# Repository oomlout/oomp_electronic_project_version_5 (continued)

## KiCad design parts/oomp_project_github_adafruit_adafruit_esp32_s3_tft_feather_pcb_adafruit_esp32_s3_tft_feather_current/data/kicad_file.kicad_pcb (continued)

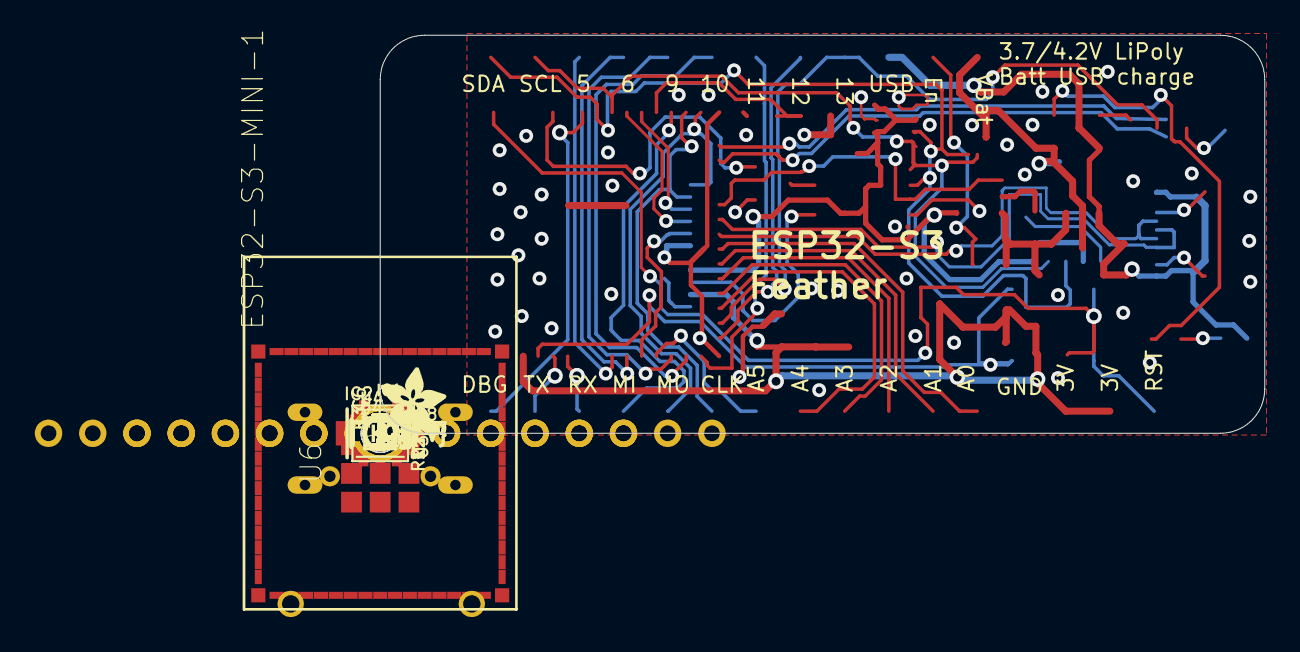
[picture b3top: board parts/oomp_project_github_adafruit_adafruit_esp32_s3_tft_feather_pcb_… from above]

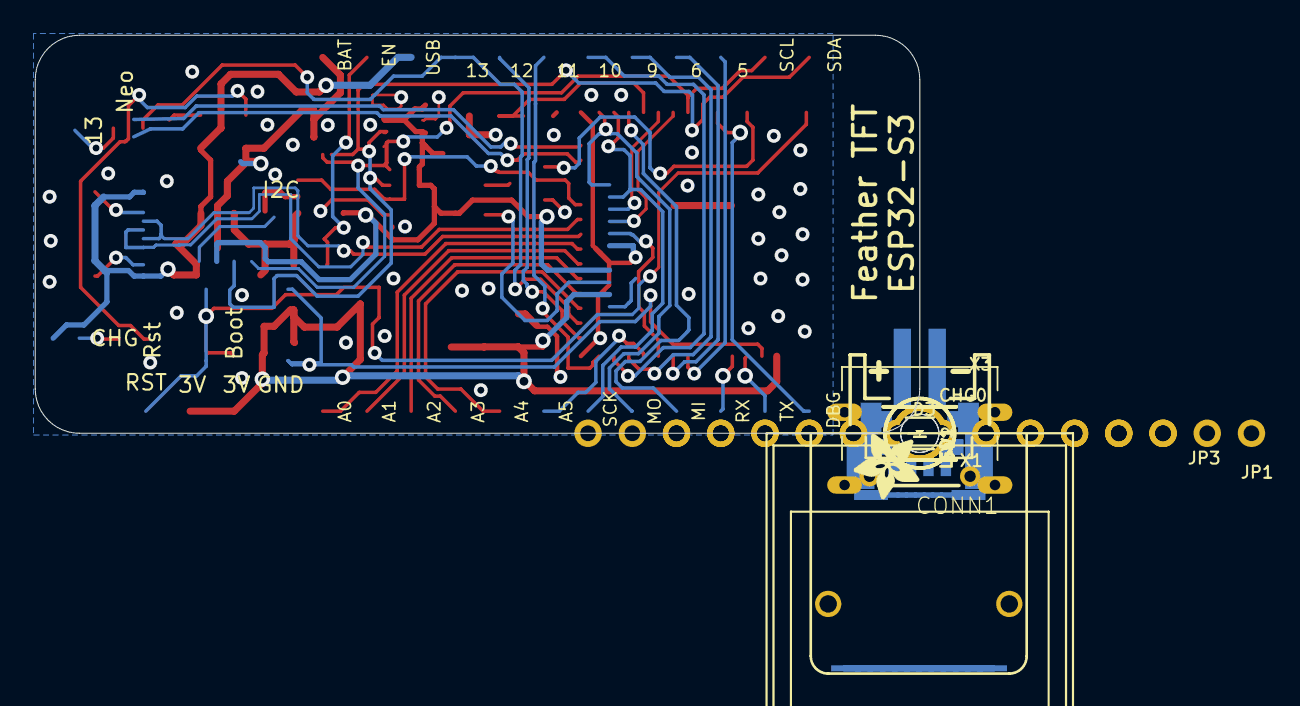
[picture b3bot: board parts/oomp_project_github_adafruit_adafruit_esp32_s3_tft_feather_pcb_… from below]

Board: 2 copper layers, 50.8 x 22.9 mm, 56 parts (16 on the bottom side), 48 nets.

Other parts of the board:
U$7: PCBFEAT-REV-040
U$9, U$54: ADAFRUIT_3.5MM
UNK_HOLE_0: dummyfp0
UNK_HOLE_1: dummyfp1

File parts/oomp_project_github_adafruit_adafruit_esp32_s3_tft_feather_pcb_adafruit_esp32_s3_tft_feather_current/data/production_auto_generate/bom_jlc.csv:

Comment,Designator,Footprint,LCSC Part #
,JP3,Adafruit ESP32-S3 TFT Feather-import-fps:1X12_ROUND_MIN,C7501588
,JP1,Adafruit ESP32-S3 TFT Feather-import-fps:1X16_ROUND_MIN,C7501270
,"U$9,U$54",Adafruit ESP32-S3 TFT Feather-import-fps:ADAFRUIT_3.5MM,
,U$7,Adafruit ESP32-S3 TFT Feather-import-fps:PCBFEAT-REV-040,
,TP1,Adafruit ESP32-S3 TFT Feather-import-fps:TESTPOINT_ROUND_1.5MM_NO,
100K,"R7,R12",Adafruit ESP32-S3 TFT Feather-import-fps:0603-NO,C25803
10K,R3,Adafruit ESP32-S3 TFT Feather-import-fps:RESPACK_4X0603,C98220
10uF,"C1,C2,C7,C9,C12",Adafruit ESP32-S3 TFT Feather-import-fps:0805-NO,
10µF,"C3,C6,C8",Adafruit ESP32-S3 TFT Feather-import-fps:0805-NO,
1Meg,R17,Adafruit ESP32-S3 TFT Feather-import-fps:0603-NO,C2907003
1uF,"C4,C5,C10,C11",Adafruit ESP32-S3 TFT Feather-import-fps:0603-NO,C5673
22,R11,Adafruit ESP32-S3 TFT Feather-import-fps:0603-NO,C23345
5.1K,"R1,R2,R4,R5,R8,R10",Adafruit ESP32-S3 TFT Feather-import-fps:0603-NO,C23186
AP2112-3.3,"U2,U5",Adafruit ESP32-S3 TFT Feather-import-fps:SOT23-5,
BME280,U4,Adafruit ESP32-S3 TFT Feather-import-fps:BME280,
BME680,IC2,Adafruit ESP32-S3 TFT Feather-import-fps:BME680,
BSS138,Q1,Adafruit ESP32-S3 TFT Feather-import-fps:SOT23-R,C52895
DISP_LCD_GENERIC_SPI_1.14IN_240X135_WRAPUNDER,DISP1,Adafruit ESP32-S3 TFT Feather-import-fps:TFT_1.14IN_240X135_WRAPUNDER,
DMG3415U,Q3,Adafruit ESP32-S3 TFT Feather-import-fps:SOT23-R,
ESP32-S3-MINI-1,U6,Adafruit ESP32-S3 TFT Feather-import-fps:QFN60_ESP32-S2-MINI-1_EXP,
FIDUCIAL_1MM,"U$34,U$35,U$55,U$56",Adafruit ESP32-S3 TFT Feather-import-fps:FIDUCIAL_1MM,
JSTPH,X1,Adafruit ESP32-S3 TFT Feather-import-fps:JSTPH2_BATT,
KMR2,"SW1,SW2",Adafruit ESP32-S3 TFT Feather-import-fps:BTN_KMR2_4.6X2.8,
LC709203F/MH,IC1,Adafruit ESP32-S3 TFT Feather-import-fps:WLCSP9,
MBR540,D4,Adafruit ESP32-S3 TFT Feather-import-fps:SOD-123,
MCP73831T-2ACI/OT,U3,Adafruit ESP32-S3 TFT Feather-import-fps:SOT23-5,
ORANGE,CHG0,Adafruit ESP32-S3 TFT Feather-import-fps:CHIPLED_0603_NOOUTLINE,
RED,D3,Adafruit ESP32-S3 TFT Feather-import-fps:CHIPLED_0603_NOOUTLINE,
STEMMA_I2C_QTRA,CONN1,Adafruit ESP32-S3 TFT Feather-import-fps:JST_SH4_RA,
USB C,X3,Adafruit ESP32-S3 TFT Feather-import-fps:USB_C_CUSB31-CFM2AX-01-X,
WS2812B_SK6805_1515,LED1,Adafruit ESP32-S3 TFT Feather-import-fps:SK6805_1515,

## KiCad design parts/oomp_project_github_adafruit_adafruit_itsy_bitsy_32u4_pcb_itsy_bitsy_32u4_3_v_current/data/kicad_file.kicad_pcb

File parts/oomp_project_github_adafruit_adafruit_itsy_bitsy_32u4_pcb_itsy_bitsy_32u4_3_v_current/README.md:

# Project adafruit/Adafruit-ItsyBitsy-32u4-PCB Itsy Bitsy 32u4 3 V current

[View the project on GitHub](https://github.com/adafruit/Adafruit-ItsyBitsy-32u4-PCB/blob/master/Itsy%20Bitsy%2032u4%203V.brd)

[Open the interactive board explorer (GitHub Pages)](https://oomlout.github.io/oomp_electronic_project_version_5/parts/oomp_project_github_adafruit_adafruit_itsy_bitsy_32u4_pcb_itsy_bitsy_32u4_3_v_current/board_explorer.html)

[Browse this project category](../../navigation/oomp/project/github/adafruit/adafruit_itsy_bitsy_32u4_pcb/itsy_bitsy_32u4_3_v/README.md)

Project adafruit/Adafruit-ItsyBitsy-32u4-PCB Itsy Bitsy 32u4 3 V current is a KiCad project containing 54 extracted component records. The catalogue matcher linked 13 physical placements to OOMP parts.

## Project snapshot

| Item | Count |
| --- | ---: |
| Components | 54 |
| PCB footprints | 26 |
| Mounting and locating holes | 2 |
| Matched OOMP mounting-hole items | 2 |
| Schematic symbols | 53 |
| Matched OOMP components | 13 |
| Unmatched physical components | 8 |
| Front-side placements | 21 |
| Back-side placements | 0 |
| Project version | `current` |
| Git ref | `master` |

## Board

[Original KiCad files](https://github.com/oomlout/oomp_electronic_project_version_5/tree/main/parts/oomp_project_github_adafruit_adafruit_itsy_bitsy_32u4_pcb_itsy_bitsy_32u4_3_v_current/data/original) · [OOMP KiCad design and local libraries](https://github.com/oomlout/oomp_electronic_project_version_5/tree/main/parts/oomp_project_github_adafruit_adafruit_itsy_bitsy_32u4_pcb_itsy_bitsy_32u4_3_v_current/data/oomp_design) · [Conversion / skipped-item report](https://github.com/oomlout/oomp_electronic_project_version_5/blob/main/parts/oomp_project_github_adafruit_adafruit_itsy_bitsy_32u4_pcb_itsy_bitsy_32u4_3_v_current/data/oomp_design/conversion_report.yaml)

The OOMP design is a separate copy. Only symbols and footprints verified against unchanged installed KiCad masters are replaced; custom and modified items are retained.

- Approximate size: **35.56 mm × 17.78 mm**
- Outline source: `KiCad Edge.Cuts`
- Placement drawing: [view `board.svg`](https://github.com/oomlout/oomp_electronic_project_version_5/blob/main/parts/oomp_project_github_adafruit_adafruit_itsy_bitsy_32u4_pcb_itsy_bitsy_32u4_3_v_current/data/generated_data/src/board.svg)
- PNG placement drawing: [view `board.png`](https://github.com/oomlout/oomp_electronic_project_version_5/blob/main/parts/oomp_project_github_adafruit_adafruit_itsy_bitsy_32u4_pcb_itsy_bitsy_32u4_3_v_current/data/generated_data/src/board.png)
- 300-pixel placement preview: [view `board_300.png`](https://github.com/oomlout/oomp_electronic_project_version_5/blob/main/parts/oomp_project_github_adafruit_adafruit_itsy_bitsy_32u4_pcb_itsy_bitsy_32u4_3_v_current/data/generated_data/src/board_300.png)
- Placement drawing with pin names: [view `board_pins.svg`](https://github.com/oomlout/oomp_electronic_project_version_5/blob/main/parts/oomp_project_github_adafruit_adafruit_itsy_bitsy_32u4_pcb_itsy_bitsy_32u4_3_v_current/data/generated_data/src/board_pins.svg)
- PNG drawing with pin names: [view `board_pins.png`](https://github.com/oomlout/oomp_electronic_project_version_5/blob/main/parts/oomp_project_github_adafruit_adafruit_itsy_bitsy_32u4_pcb_itsy_bitsy_32u4_3_v_current/data/generated_data/src/board_pins.png)
- 300-pixel pin preview: [view `board_pins_300.png`](https://github.com/oomlout/oomp_electronic_project_version_5/blob/main/parts/oomp_project_github_adafruit_adafruit_itsy_bitsy_32u4_pcb_itsy_bitsy_32u4_3_v_current/data/generated_data/src/board_pins_300.png)
- Bottom placement drawing: [view `board_bottom.svg`](https://github.com/oomlout/oomp_electronic_project_version_5/blob/main/parts/oomp_project_github_adafruit_adafruit_itsy_bitsy_32u4_pcb_itsy_bitsy_32u4_3_v_current/data/generated_data/src/board_bottom.svg)
- Bottom PNG placement drawing: [view `board_bottom.png`](https://github.com/oomlout/oomp_electronic_project_version_5/blob/main/parts/oomp_project_github_adafruit_adafruit_itsy_bitsy_32u4_pcb_itsy_bitsy_32u4_3_v_current/data/generated_data/src/board_bottom.png)
- 300-pixel bottom preview: [view `board_bottom_300.png`](https://github.com/oomlout/oomp_electronic_project_version_5/blob/main/parts/oomp_project_github_adafruit_adafruit_itsy_bitsy_32u4_pcb_itsy_bitsy_32u4_3_v_current/data/generated_data/src/board_bottom_300.png)
- Bottom placement drawing with pin names: [view `board_pins_bottom.svg`](https://github.com/oomlout/oomp_electronic_project_version_5/blob/main/parts/oomp_project_github_adafruit_adafruit_itsy_bitsy_32u4_pcb_itsy_bitsy_32u4_3_v_current/data/generated_data/src/board_pins_bottom.svg)
- Bottom PNG drawing with pin names: [view `board_pins_bottom.png`](https://github.com/oomlout/oomp_electronic_project_version_5/blob/main/parts/oomp_project_github_adafruit_adafruit_itsy_bitsy_32u4_pcb_itsy_bitsy_32u4_3_v_current/data/generated_data/src/board_pins_bottom.png)
- 300-pixel bottom pin preview: [view `board_pins_bottom_300.png`](https://github.com/oomlout/oomp_electronic_project_version_5/blob/main/parts/oomp_project_github_adafruit_adafruit_itsy_bitsy_32u4_pcb_itsy_bitsy_32u4_3_v_current/data/generated_data/src/board_pins_bottom_300.png)
- Mechanical drawing: [view `board_mechanical.svg`](https://github.com/oomlout/oomp_electronic_project_version_5/blob/main/parts/oomp_project_github_adafruit_adafruit_itsy_bitsy_32u4_pcb_itsy_bitsy_32u4_3_v_current/data/generated_data/src/board_mechanical.svg)
- Mechanical PNG: [view `board_mechanical.png`](https://github.com/oomlout/oomp_electronic_project_version_5/blob/main/parts/oomp_project_github_adafruit_adafruit_itsy_bitsy_32u4_pcb_itsy_bitsy_32u4_3_v_current/data/generated_data/src/board_mechanical.png)
- 300-pixel mechanical preview: [view `board_mechanical_300.png`](https://github.com/oomlout/oomp_electronic_project_version_5/blob/main/parts/oomp_project_github_adafruit_adafruit_itsy_bitsy_32u4_pcb_itsy_bitsy_32u4_3_v_current/data/generated_data/src/board_mechanical_300.png)
- Open the board explorer on GitHub Pages: [explore this board](https://oomlout.github.io/oomp_electronic_project_version_5/parts/oomp_project_github_adafruit_adafruit_itsy_bitsy_32u4_pcb_itsy_bitsy_32u4_3_v_current/board_explorer.html)
- InteractiveHtmlBom generation is configured; install KiCad or set `KICAD_PYTHON` to its bundled Python to build `data/interactivehtmlbom/ibom.html`.

## Board with pins

## Bottom board with pins

The bottom view is mirrored horizontally so it is shown as viewed from beneath the assembled board.

## Mechanical layer

The table uses a board-relative origin at the minimum X/Y point of `Edge.Cuts`. This point is shown as **0,0** in the mechanical drawing; X increases right and Y increases down. Original KiCad coordinates are retained alongside it.

### Diameter 0.7 mm holes

| OOMP reference | Source | Name | Classification | Role | Board X (mm) | Board Y (mm) | OOMP part |
| --- | --- | --- | --- | --- | ---: | ---: | --- |
| `MH1` | `X3` | Mounting Hole 0.7 mm Round Unplated | `mechanical / mounting_hole / 0_7_mm / round / unplated` | locating | 4.445 | 6.940 | [`mechanical_mounting_hole_0_7_mm_round_unplated`](https://github.com/oomlout/oomp_electronic_version_5/tree/main/parts/mechanical_mounting_hole_0_7_mm_round_unplated) |
| `MH2` | `X3` | Mounting Hole 0.7 mm Round Unplated | `mechanical / mounting_hole / 0_7_mm / round / unplated` | locating | 4.445 | 10.840 | [`mechanical_mounting_hole_0_7_mm_round_unplated`](https://github.com/oomlout/oomp_electronic_version_5/tree/main/parts/mechanical_mounting_hole_0_7_mm_round_unplated) |

## Bill of materials

| References | Quantity | Description | Value | Footprint | OOMP part |
| --- | ---: | --- | --- | --- | --- |
| C6, C8 | 2 | Capacitor 10 uF 0805 | 10µF | `Itsy Bitsy 32u4 3V-import-fps:0805-NO` | [`electronic_capacitor_0805_10_micro_farad`](https://github.com/oomlout/oomp_electronic_version_5/tree/main/parts/electronic_capacitor_0805_10_micro_farad) |
| C7, C14 | 2 | Capacitor 1 uF 0603 | 1uF | `Itsy Bitsy 32u4 3V-import-fps:0603-NO` | [`electronic_capacitor_0603_1_micro_farad`](https://github.com/oomlout/oomp_electronic_version_5/tree/main/parts/electronic_capacitor_0603_1_micro_farad) |
| C9 | 1 | Capacitor 10 uF 0805 | 10uF | `Itsy Bitsy 32u4 3V-import-fps:0805-NO` | [`electronic_capacitor_0805_10_micro_farad`](https://github.com/oomlout/oomp_electronic_version_5/tree/main/parts/electronic_capacitor_0805_10_micro_farad) |
| D1, D4 | 2 | MBR120 | MBR120 | `Itsy Bitsy 32u4 3V-import-fps:SOD-123` | unmatched |
| IC1 | 1 | ATMEGA32U4-MU | ATMEGA32U4-MU | `Itsy Bitsy 32u4 3V-import-fps:TQFN44_7MM` | unmatched |
| IC2 | 1 | 74HCT1G125DBV | 74HCT1G125DBV | `Itsy Bitsy 32u4 3V-import-fps:SOT23-5` | unmatched |
| JP1 | 1 | Connector Header PH2.54-1X5P-H25 |  | `Itsy Bitsy 32u4 3V-import-fps:1X05_ROUND` | [`electronic_connector_header_2_54_mm_pitch_through_hole_5_pin`](https://github.com/oomlout/oomp_electronic_version_5/tree/main/parts/electronic_connector_header_2_54_mm_pitch_through_hole_5_pin) |
| JP2, JP4 | 2 | Connector Header KH-2.54PH180-1X14P-L11.5 |  | `Itsy Bitsy 32u4 3V-import-fps:1X14_ROUND70` | [`electronic_connector_header_2_54_mm_pitch_through_hole_14_pin`](https://github.com/oomlout/oomp_electronic_version_5/tree/main/parts/electronic_connector_header_2_54_mm_pitch_through_hole_14_pin) |
| L0 | 1 | LED Red 0805 | RED | `Itsy Bitsy 32u4 3V-import-fps:CHIPLED_0805_NOOUTLINE` | [`electronic_led_0805_red`](https://github.com/oomlout/oomp_electronic_version_5/tree/main/parts/electronic_led_0805_red) |
| R4, R5 | 2 | Resistor 22 Ohm 0603 | 22 | `Itsy Bitsy 32u4 3V-import-fps:0603-NO` | [`electronic_resistor_0603_22_ohm`](https://github.com/oomlout/oomp_electronic_version_5/tree/main/parts/electronic_resistor_0603_22_ohm) |
| R7 | 1 | Resistor 2200 Ohm 0603 | 2.2K | `Itsy Bitsy 32u4 3V-import-fps:0603-NO` | [`electronic_resistor_0603_2200_ohm`](https://github.com/oomlout/oomp_electronic_version_5/tree/main/parts/electronic_resistor_0603_2200_ohm) |
| R9 | 1 | Resistor 100000 Ohm 0603 | 100k | `Itsy Bitsy 32u4 3V-import-fps:0603-NO` | [`electronic_resistor_0603_100000_ohm`](https://github.com/oomlout/oomp_electronic_version_5/tree/main/parts/electronic_resistor_0603_100000_ohm) |
| SW1 | 1 | SPST_TACT-KMR2 | SPST_TACT-KMR2 | `Itsy Bitsy 32u4 3V-import-fps:KMR2` | unmatched |
| U2 | 1 | AP2112K | AP2112K | `Itsy Bitsy 32u4 3V-import-fps:SOT23-5` | unmatched |
| X3 | 1 | microUSB | microUSB | `Itsy Bitsy 32u4 3V-import-fps:4UCONN_20329_V2` | unmatched |
| Y1 | 1 | 8MHz | 8MHz | `Itsy Bitsy 32u4 3V-import-fps:RESONATOR-SMD` | unmatched |

## Main nets

| Net | Pads | Components |
| --- | ---: | --- |
| `GND` | 27 | C6, C7, C8, C9, C14, IC1, IC2, JP1, JP2, JP4, L0, SW1, U2, X3, Y1 |
| `+3V3` | 11 | C7, C8, C9, IC1, JP4, U2 |
| `VMAX` | 7 | C6, D1, D4, IC2, JP4, R9, U2 |
| `RST` | 4 | IC1, JP4, SW1 |
| `VBUS` | 4 | D1, IC1, JP2, X3 |
| `AREF` | 3 | C14, IC1, JP4 |
| `D13` | 3 | IC1, JP2, R7 |
| `EN` | 3 | JP1, R9, U2 |
| `A0` | 2 | IC1, JP4 |
| `A1` | 2 | IC1, JP4 |
| `A2` | 2 | IC1, JP4 |
| `A3` | 2 | IC1, JP4 |
| `A4` | 2 | IC1, JP4 |
| `A5` | 2 | IC1, JP4 |
| `D+` | 2 | IC1, R5 |
| `D-` | 2 | IC1, R4 |
| `D0` | 2 | IC1, JP2 |
| `D1` | 2 | IC1, JP2 |
| `D10` | 2 | IC1, JP2 |
| `D11` | 2 | IC1, JP2 |

## Design notes

- The extracted board outline is approximately 35.56 mm by 17.78 mm.
- Placement data contains 21 front-side and 0 back-side components.

## Review notes

- 8 physical component records are not yet matched to an OOMP part.

- Part identities needing a manufacturer/LCSC decision: [`lcsc_review.yaml`](https://github.com/oomlout/oomp_electronic_project_version_5/blob/main/parts/oomp_project_github_adafruit_adafruit_itsy_bitsy_32u4_pcb_itsy_bitsy_32u4_3_v_current/data/generated_data/lcsc_review.yaml)
- Browser-only research and datasheet queue: [`browser_research_queue.md`](https://github.com/oomlout/oomp_electronic_project_version_5/blob/main/parts/oomp_project_github_adafruit_adafruit_itsy_bitsy_32u4_pcb_itsy_bitsy_32u4_3_v_current/data/generated_data/browser_research_queue.md)

## Generated source bundle

- Project image assets: [`data/generated_data/src`](https://github.com/oomlout/oomp_electronic_project_version_5/tree/main/parts/oomp_project_github_adafruit_adafruit_itsy_bitsy_32u4_pcb_itsy_bitsy_32u4_3_v_current/data/generated_data/src)
- Copied component source manifest: `data/project_source/manifest.yaml` (generated locally and ignored by Git)
- Matched OOMP source parts copied: 8

## Source files

- Schematic: `data/kicad_file.kicad_sch`
- PCB: `data/kicad_file.kicad_pcb`

---

Generated deterministically by `kicad_agents.project_summary_agent`; no LLM-authored content is used.

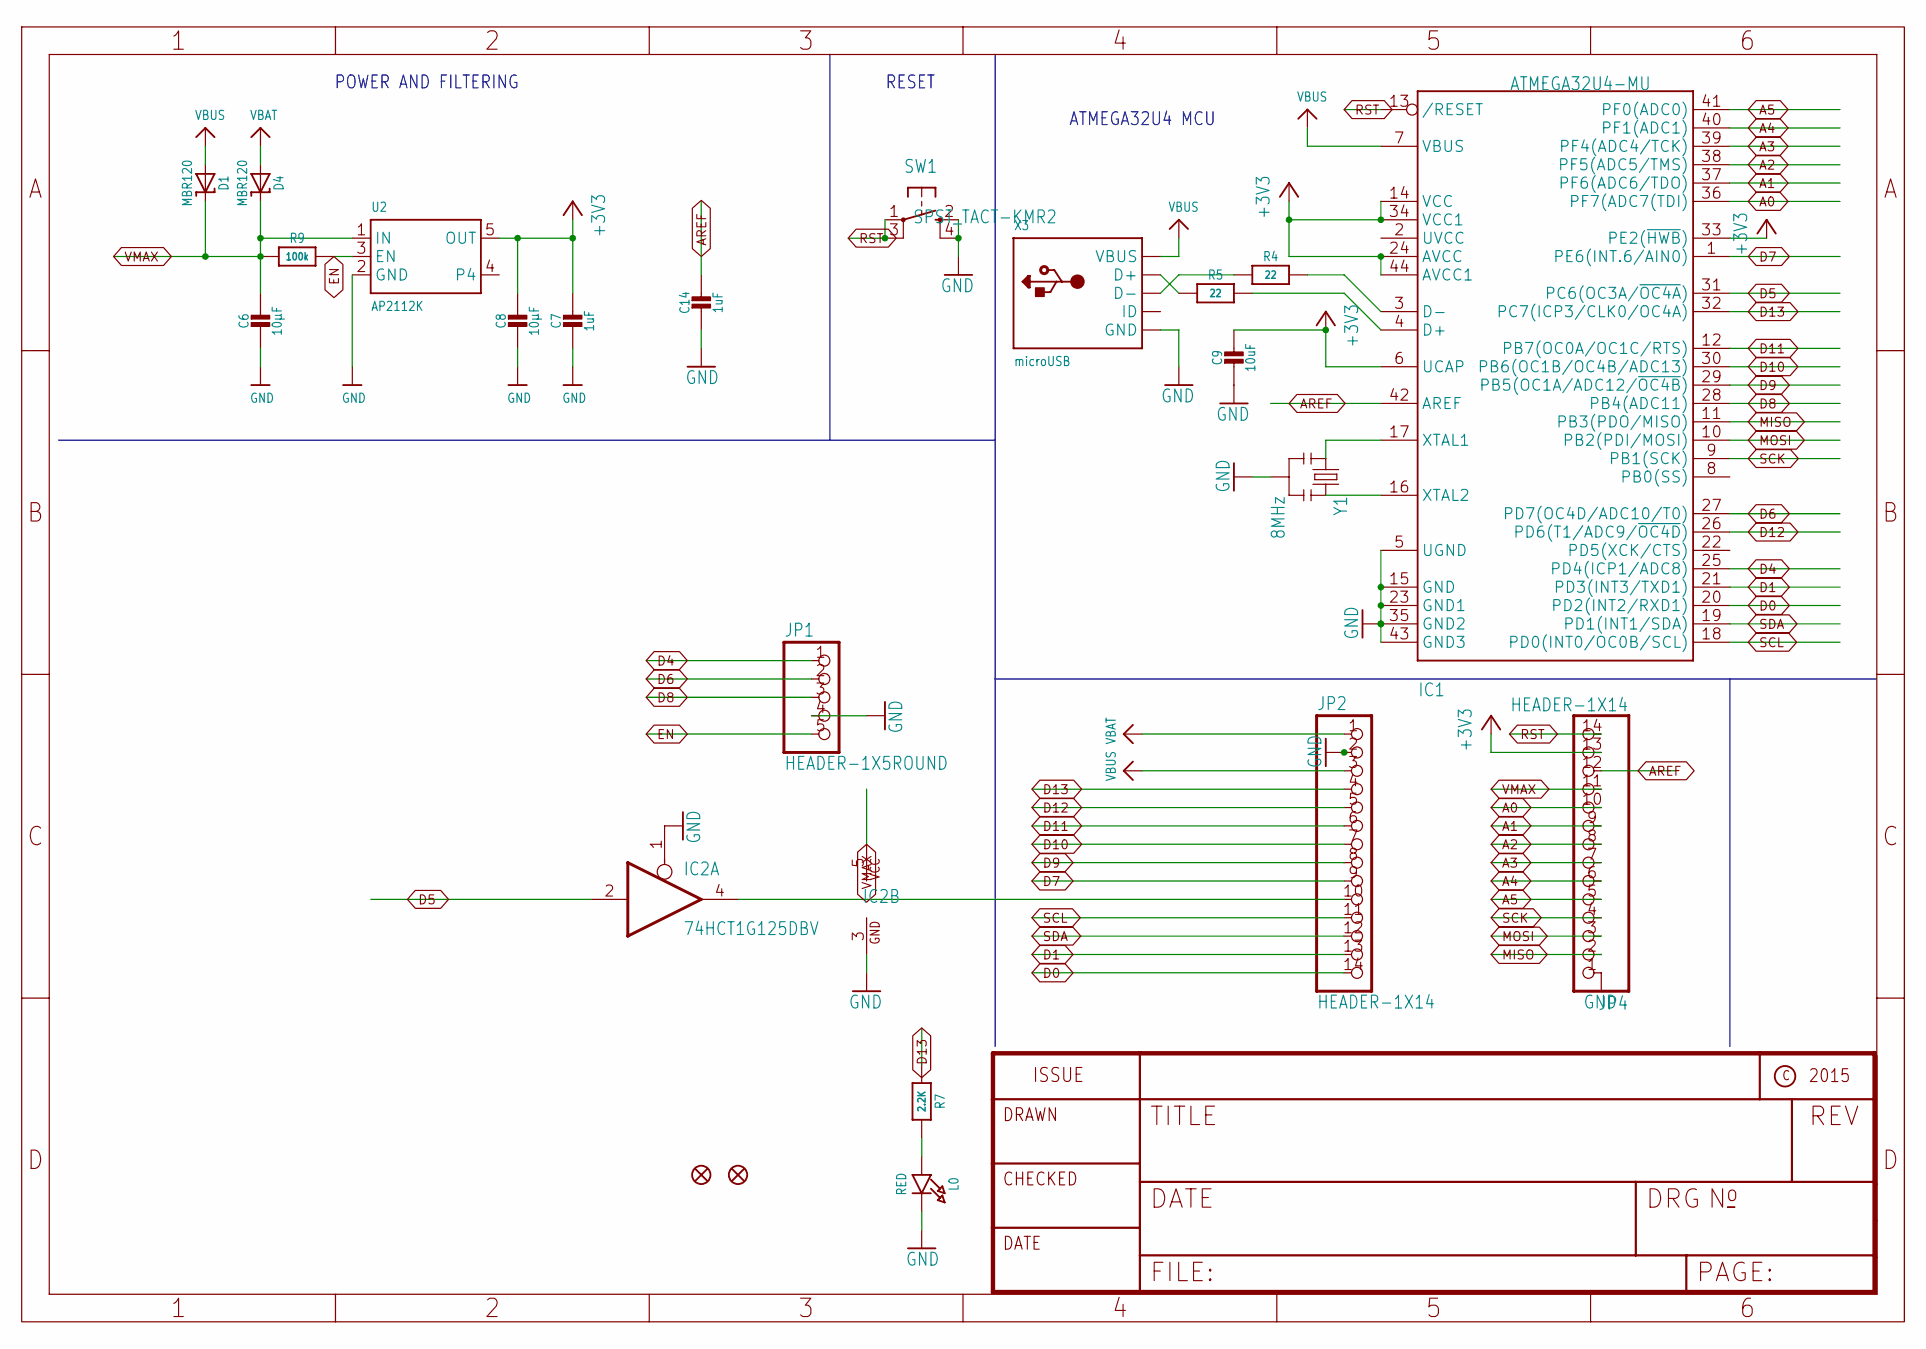
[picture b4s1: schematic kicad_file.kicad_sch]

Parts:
C6, C8: 10µF; 0805-NO
C7, C14: 1uF; 0603-NO
C9: 10uF; 0805-NO
D1, D4: MBR120; SOD-123
IC1: ATMEGA32U4-MU; TQFN44_7MM
IC2: 74HCT1G125DBV; SOT23-5
JP1: HEADER-1X5ROUND; 1X05_ROUND
JP2, JP4: HEADER-1X14; 1X14_ROUND70
L0: RED; CHIPLED_0805_NOOUTLINE
R4, R5: 22; 0603-NO
R7: 2.2K; 0603-NO
R9: 100k; 0603-NO
SW1: SPST_TACT-KMR2; KMR2
U2: AP2112K; SOT23-5
U$34, U$35: FIDUCIAL""; FIDUCIAL_1MM
X3: microUSB; 4UCONN_20329_V2
Y1: 8MHz; RESONATOR-SMD

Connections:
+3V3: C7.1, C8.1, C9.1, IC1.6 (UCAP), IC1.14 (VCC), IC1.24 (AVCC), IC1.33 (PE2(~HWB)), IC1.34 (VCC1), IC1.44 (AVCC1), JP4.13, U2.5 (OUT)
A0: IC1.36 (PF7(ADC7(TDI)), JP4.10
A1: IC1.37 (PF6(ADC6/TDO)), JP4.9
A2: IC1.38 (PF5(ADC5/TMS)), JP4.8
A3: IC1.39 (PF4(ADC4/TCK)), JP4.7
A4: IC1.40 (PF1(ADC1)), JP4.6
A5: IC1.41 (PF0(ADC0)), JP4.5
AREF: C14.1, IC1.42 (AREF), JP4.12
D0: IC1.20 (PD2(INT2/RXD1)), JP2.14
D1: IC1.21 (PD3(INT3/TXD1)), JP2.13
D4: IC1.25 (PD4(ICP1/ADC8)), JP1.1
D5: IC1.31 (PC6(OC3A/~OC4A)), IC2.2 (I)
D5_OUT: IC2.4 (O), JP2.10
D6: IC1.27 (PD7(OC4D/ADC10/T0)), JP1.2
D7: IC1.1 (PE6(INT.6/AIN0)), JP2.9
D8: IC1.28 (PB4(ADC11)), JP1.3
D9: IC1.29 (PB5(OC1A/ADC12/~OC4B)), JP2.8
D10: IC1.30 (PB6(OC1B/OC4B/ADC13)), JP2.7
D11: IC1.12 (PB7(OC0A/OC1C/RTS)), JP2.6
D12: IC1.26 (PD6(T1/ADC9/~OC4D)), JP2.5
D13: IC1.32 (PC7(ICP3/CLK0/OC4A)), JP2.4, R7.1
D+: IC1.4 (D+), R5.2
D-: IC1.3 (D-), R4.2
EN: JP1.5, R9.2, U2.3 (EN)
GND: C6.2, C7.2, C8.2, C9.2, C14.2, IC1.5 (UGND), IC1.15 (GND), IC1.23 (GND1), IC1.35 (GND2), IC1.43 (GND3), IC2.1 (OE), IC2.3 (GND), JP1.4, JP2.2, JP4.1, L0.C, SW1.2 (S), SW1.4 (S1), U2.2 (GND), X3.BASE@1 (GND), X3.BASE@2 (GND), X3.GND, X3.SPRT@1 (GND), X3.SPRT@2 (GND), X3.SPRT@3 (GND), X3.SPRT@4 (GND), Y1.2
MISO: IC1.11 (PB3(PDO/MISO)), JP4.2
MOSI: IC1.10 (PB2(PDI/MOSI)), JP4.3
unnamed: L0.A, R7.2
unnamed: IC1.16 (XTAL2), Y1.3
unnamed: IC1.17 (XTAL1), Y1.1
unnamed: R5.1, X3.D+
unnamed: R4.1, X3.D-
RST: IC1.13 (/RESET), JP4.14, SW1.1, SW1.3 (P1)
SCK: IC1.9 (PB1(SCK)), JP4.4
SCL: IC1.18 (PD0(INT0/OC0B/SCL)), JP2.11
SDA: IC1.19 (PD1(INT1/SDA)), JP2.12
VBAT: D4.A, JP2.1
VBUS: D1.A, IC1.7 (VBUS), JP2.3, X3.VBUS
VMAX: C6.1, D1.C, D4.C, IC2.5 (VCC), JP4.11, R9.1, U2.1 (IN)

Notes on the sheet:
POWER AND FILTERING
RESET
ATMEGA32U4 MCU

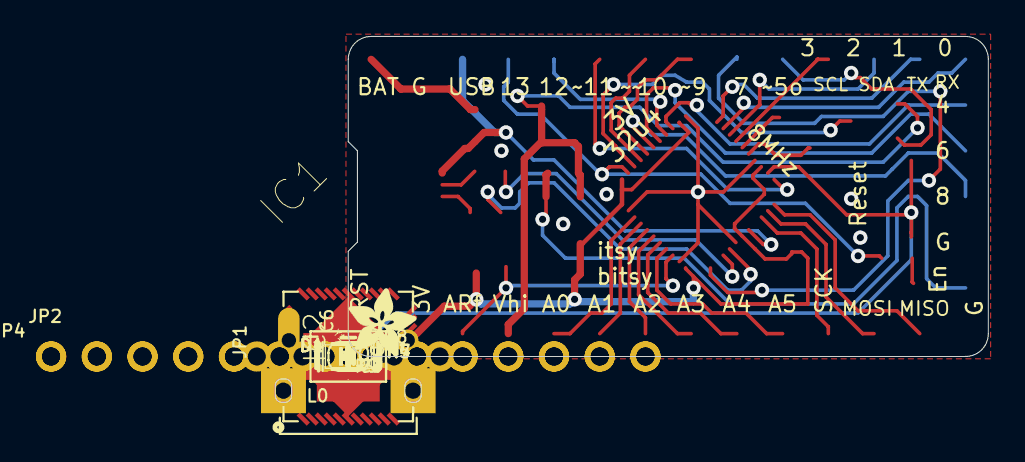
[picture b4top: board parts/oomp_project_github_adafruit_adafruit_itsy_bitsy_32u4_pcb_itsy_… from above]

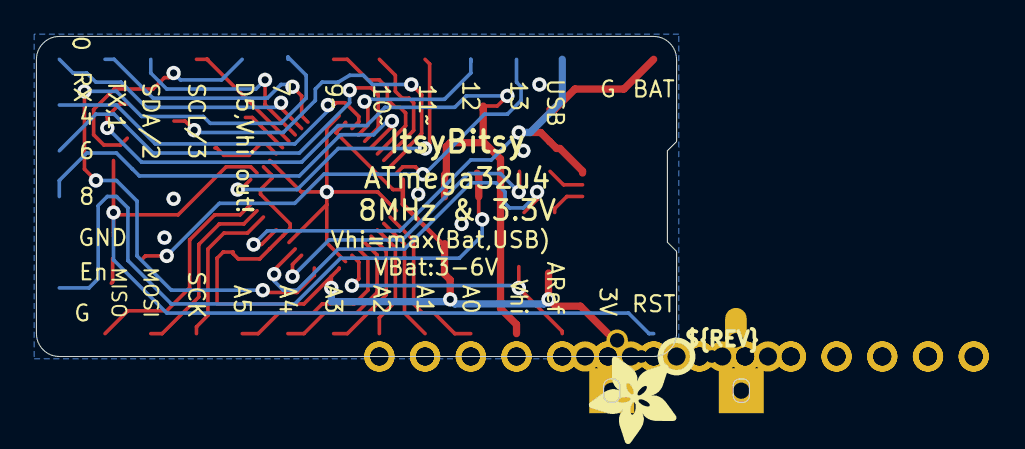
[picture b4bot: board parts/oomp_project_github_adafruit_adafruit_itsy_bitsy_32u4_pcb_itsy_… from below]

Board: 2 copper layers, 35.6 x 17.8 mm, 26 parts (2 on the bottom side), 39 nets.

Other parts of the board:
U$2: PCBFEAT-REV-040
U$4: ADAFRUIT_5MM
U$7: ADAFRUIT_3.5MM

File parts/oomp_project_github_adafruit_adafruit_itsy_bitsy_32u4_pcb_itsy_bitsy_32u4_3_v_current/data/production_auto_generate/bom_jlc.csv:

Comment,Designator,Footprint,LCSC Part #
,JP1,Itsy Bitsy 32u4 3V-import-fps:1X05_ROUND,C42431835
,"JP2,JP4",Itsy Bitsy 32u4 3V-import-fps:1X14_ROUND70,C2905490
,U$7,Itsy Bitsy 32u4 3V-import-fps:ADAFRUIT_3.5MM,
,U$4,Itsy Bitsy 32u4 3V-import-fps:ADAFRUIT_5MM,
,U$2,Itsy Bitsy 32u4 3V-import-fps:PCBFEAT-REV-040,
100k,R9,Itsy Bitsy 32u4 3V-import-fps:0603-NO,C25803
10uF,C9,Itsy Bitsy 32u4 3V-import-fps:0805-NO,
10µF,"C6,C8",Itsy Bitsy 32u4 3V-import-fps:0805-NO,
1uF,"C7,C14",Itsy Bitsy 32u4 3V-import-fps:0603-NO,C5673
2.2K,R7,Itsy Bitsy 32u4 3V-import-fps:0603-NO,C4190
22,"R4,R5",Itsy Bitsy 32u4 3V-import-fps:0603-NO,C23345
74HCT1G125DBV,IC2,Itsy Bitsy 32u4 3V-import-fps:SOT23-5,
8MHz,Y1,Itsy Bitsy 32u4 3V-import-fps:RESONATOR-SMD,
AP2112K,U2,Itsy Bitsy 32u4 3V-import-fps:SOT23-5,
ATMEGA32U4-MU,IC1,Itsy Bitsy 32u4 3V-import-fps:TQFN44_7MM,
"FIDUCIAL""""","U$34,U$35",Itsy Bitsy 32u4 3V-import-fps:FIDUCIAL_1MM,
MBR120,"D1,D4",Itsy Bitsy 32u4 3V-import-fps:SOD-123,
microUSB,X3,Itsy Bitsy 32u4 3V-import-fps:4UCONN_20329_V2,
RED,L0,Itsy Bitsy 32u4 3V-import-fps:CHIPLED_0805_NOOUTLINE,
SPST_TACT-KMR2,SW1,Itsy Bitsy 32u4 3V-import-fps:KMR2,

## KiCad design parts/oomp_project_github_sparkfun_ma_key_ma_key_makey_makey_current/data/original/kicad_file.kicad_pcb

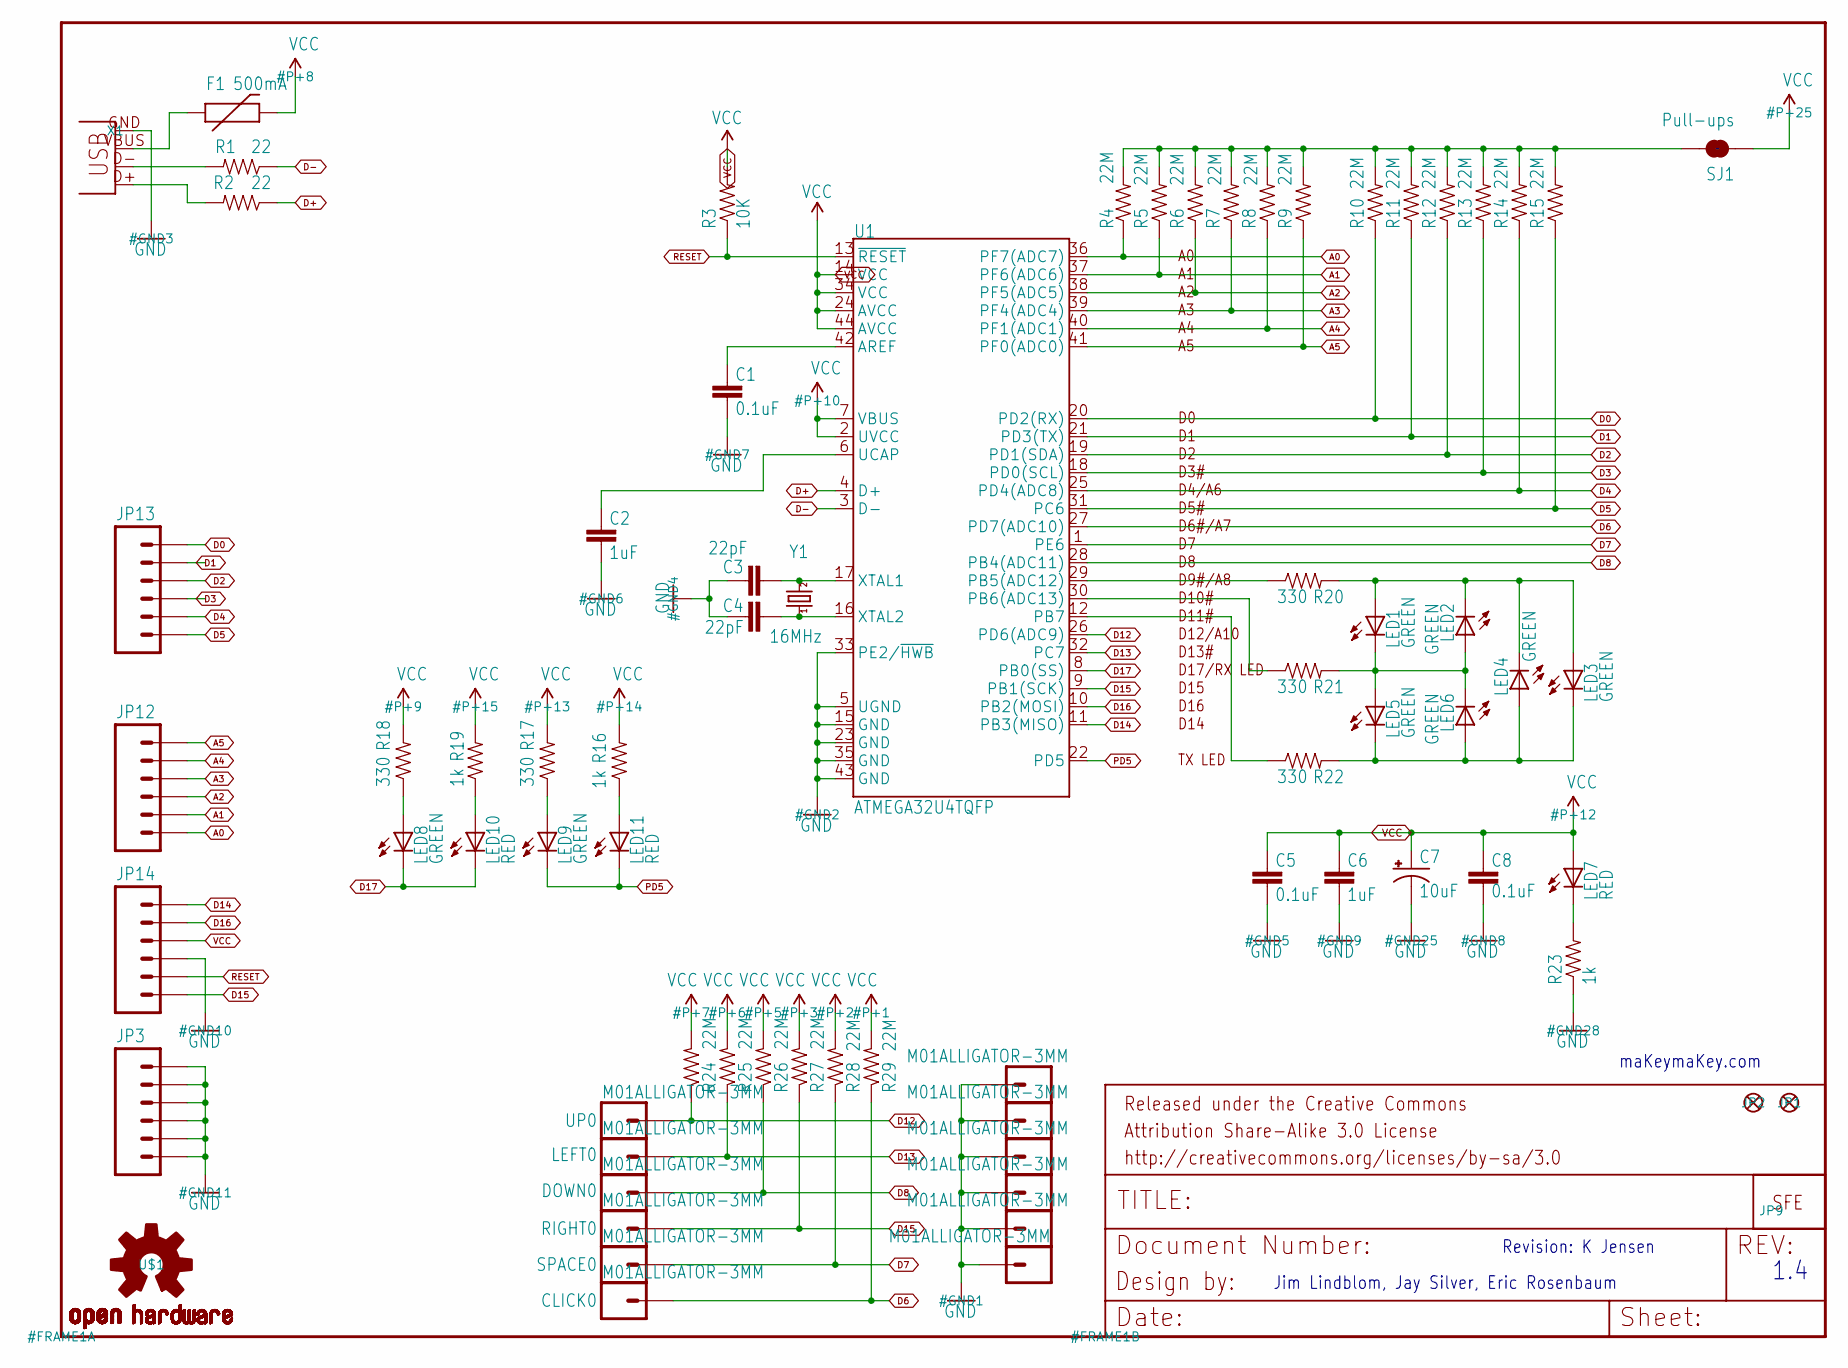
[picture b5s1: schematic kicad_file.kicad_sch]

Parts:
C1, C5, C8: 0.1uF; 0603-CAP
C2, C6: 1uF; 0603-CAP
C3, C4: 22pF; 0603-CAP
C7: 10uF; EIA3216
CLICK0: M01ALLIGATOR-3MM; 1X01_ALLIGATOR_3MM
DOWN0: M01ALLIGATOR-3MM; 1X01_ALLIGATOR_3MM
F1: 500mA; PTC-1206-WIDE
JP1, JP2: FIDUCIALUFIDUCIAL; MICRO-FIDUCIAL
JP3, JP12, JP13, JP14: M06SMD-STRAIGHT-COMBO; 1X06_SMD_STRAIGHT_COMBO
JP5, JP6, JP7, JP8, JP10, JP11: M01ALLIGATOR-3MM; 1X01_ALLIGATOR_3MM
JP9: LOGO-SFENEW; SFE-NEW-WEBLOGO
LED1, LED2, LED3, LED4, LED5, LED6: GREEN; LED-1206-BOTTOM
LED7, LED10, LED11: RED; LED-0603
LED8, LED9: GREEN; LED-0603
LEFT0: M01ALLIGATOR-3MM; 1X01_ALLIGATOR_3MM
R1, R2: 22; 0603-RES
R3: 10K; 0603-RES
R4, R5, R6, R7, R8, R9, R10, R11, R12, R13, R14, R15, R24, R25, R26, R27, R28, R29: 22M; 0603-RES
R16, R19, R23: 1k; 0603-RES
R17, R18, R20, R21, R22: 330; 0603-RES
RIGHT0: M01ALLIGATOR-3MM; 1X01_ALLIGATOR_3MM
SJ1: Pull-ups; SJ_2S-TRACE
SPACE0: M01ALLIGATOR-3MM; 1X01_ALLIGATOR_3MM
U1: ATMEGA32U4TQFP; TQFP44
U$1: OSHW-LOGOM; OSHW-LOGO-M
UP0: M01ALLIGATOR-3MM; 1X01_ALLIGATOR_3MM
X1: USBSMD; USB-MINIB
Y1: 16MHz; CRYSTAL-SMD-5X3

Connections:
A0: JP12.1, JP12.1-2 (1), R4.1, U1.36 (PF7(ADC7))
A1: JP12.2, JP12.2-2 (2), R5.1, U1.37 (PF6(ADC6))
A2: JP12.3, JP12.3-2 (3), R6.1, U1.38 (PF5(ADC5))
A3: JP12.4, JP12.4-2 (4), R7.1, U1.39 (PF4(ADC4))
A4: JP12.5, JP12.5-2 (5), R8.1, U1.40 (PF1(ADC1))
A5: JP12.6, JP12.6-2 (6), R9.1, U1.41 (PF0(ADC0))
AREF: C1.2, U1.42 (AREF)
D0: JP13.6, JP13.6-2 (6), R10.1, U1.20 (PD2(RX))
D1: JP13.5, JP13.5-2 (5), R11.1, U1.21 (PD3(TX))
D2: JP13.4, JP13.4-2 (4), R12.1, U1.19 (PD1(SDA))
D3: JP13.3, JP13.3-2 (3), R13.1, U1.18 (PD0(SCL))
D4: JP13.2, JP13.2-2 (2), R14.1, U1.25 (PD4(ADC8))
D5: JP13.1, JP13.1-2 (1), R15.1, U1.31 (PC6)
D6: CLICK0.1@0, CLICK0.1@2, R29.1, U1.27 (PD7(ADC10))
D7: R28.1, SPACE0.1@0, SPACE0.1@2, U1.1 (PE6)
D8: DOWN0.1@0, DOWN0.1@2, R26.1, U1.28 (PB4(ADC11))
D9: R20.1, U1.29 (PB5(ADC12))
D10: R21.1, U1.30 (PB6(ADC13))
D11: R22.1, U1.12 (PB7)
D12: R24.1, U1.26 (PD6(ADC9)), UP0.1@0, UP0.1@2
D13: LEFT0.1@0, LEFT0.1@2, R25.1, U1.32 (PC7)
D14: JP14.6, JP14.6-2 (6), U1.11 (PB3(MISO))
D15: JP14.1, JP14.1-2 (1), R27.1, RIGHT0.1@0, RIGHT0.1@2, U1.9 (PB1(SCK))
D16: JP14.5, JP14.5-2 (5), U1.10 (PB2(MOSI))
D17: LED8.C, LED10.C, U1.8 (PB0(SS))
D+: R2.1, U1.4 (D+)
D-: R1.1, U1.3 (D-)
GND: C1.1, C2.1, C3.2, C4.2, C5.1, C6.1, C7.C (-), C8.1, JP3.1, JP3.1-2 (1), JP3.2, JP3.2-2 (2), JP3.3, JP3.3-2 (3), JP3.4, JP3.4-2 (4), JP3.5, JP3.5-2 (5), JP3.6, JP3.6-2 (6), JP5.1@0, JP5.1@2, JP6.1@0, JP6.1@2, JP7.1@0, JP7.1@2, JP8.1@0, JP8.1@2, JP10.1@0, JP10.1@2, JP11.1@0, JP11.1@2, JP14.3, JP14.3-2 (3), R23.1, U1.5 (UGND), U1.15 (GND), U1.23 (GND), U1.33 (PE2/~HWB), U1.35 (GND), U1.43 (GND), X1.GND
unnamed: C4.1, U1.16 (XTAL2), Y1.1
unnamed: C3.1, U1.17 (XTAL1), Y1.3 (2)
unnamed: LED8.A, R18.1
unnamed: C2.2, U1.6 (UCAP)
unnamed: F1.1, X1.VBUS
unnamed: R1.2, X1.D-
unnamed: LED7.C, R23.2
unnamed: R2.2, X1.D+
unnamed: LED11.A, R16.1
unnamed: LED10.A, R19.1
unnamed: LED9.A, R17.1
unnamed: LED1.C, LED2.A, LED5.A, LED6.C, R21.2
unnamed: LED1.A, LED2.C, LED3.A, LED4.C, R20.2
unnamed: LED3.C, LED4.A, LED5.C, LED6.A, R22.2
PD5: LED9.C, LED11.C, U1.22 (PD5)
PULL-UP: R4.2, R5.2, R6.2, R7.2, R8.2, R9.2, R10.2, R11.2, R12.2, R13.2, R14.2, R15.2, SJ1.2
RESET: JP14.2, JP14.2-2 (2), R3.1, U1.13 (~RESET)
VCC: C5.2, C6.2, C7.A (+), C8.2, F1.2, JP14.4, JP14.4-2 (4), LED7.A, R3.2, R16.2, R17.2, R18.2, R19.2, R24.2, R25.2, R26.2, R27.2, R28.2, R29.2, SJ1.1, U1.2 (UVCC), U1.7 (VBUS), U1.14 (VCC), U1.24 (AVCC), U1.34 (VCC), U1.44 (AVCC)

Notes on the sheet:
1.4
maKeymaKey.com
Revision: K Jensen
Jim Lindblom, Jay Silver, Eric Rosenbaum

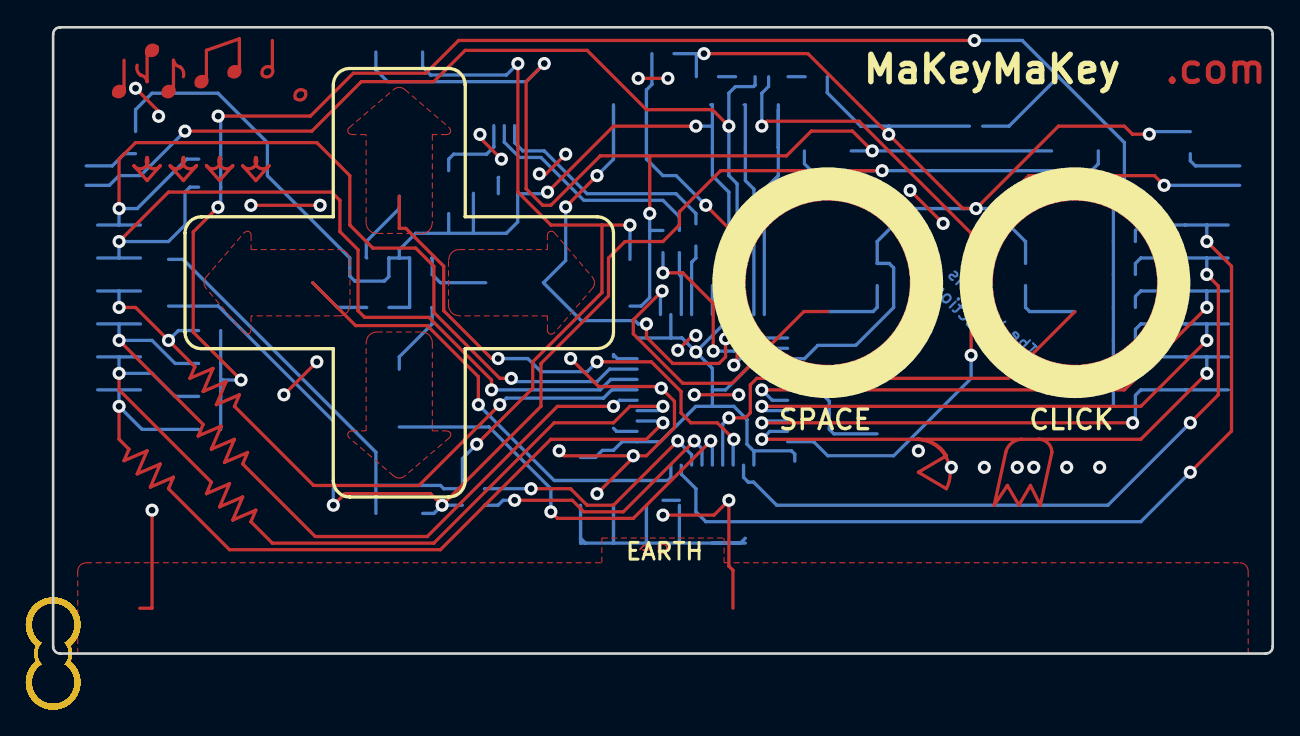
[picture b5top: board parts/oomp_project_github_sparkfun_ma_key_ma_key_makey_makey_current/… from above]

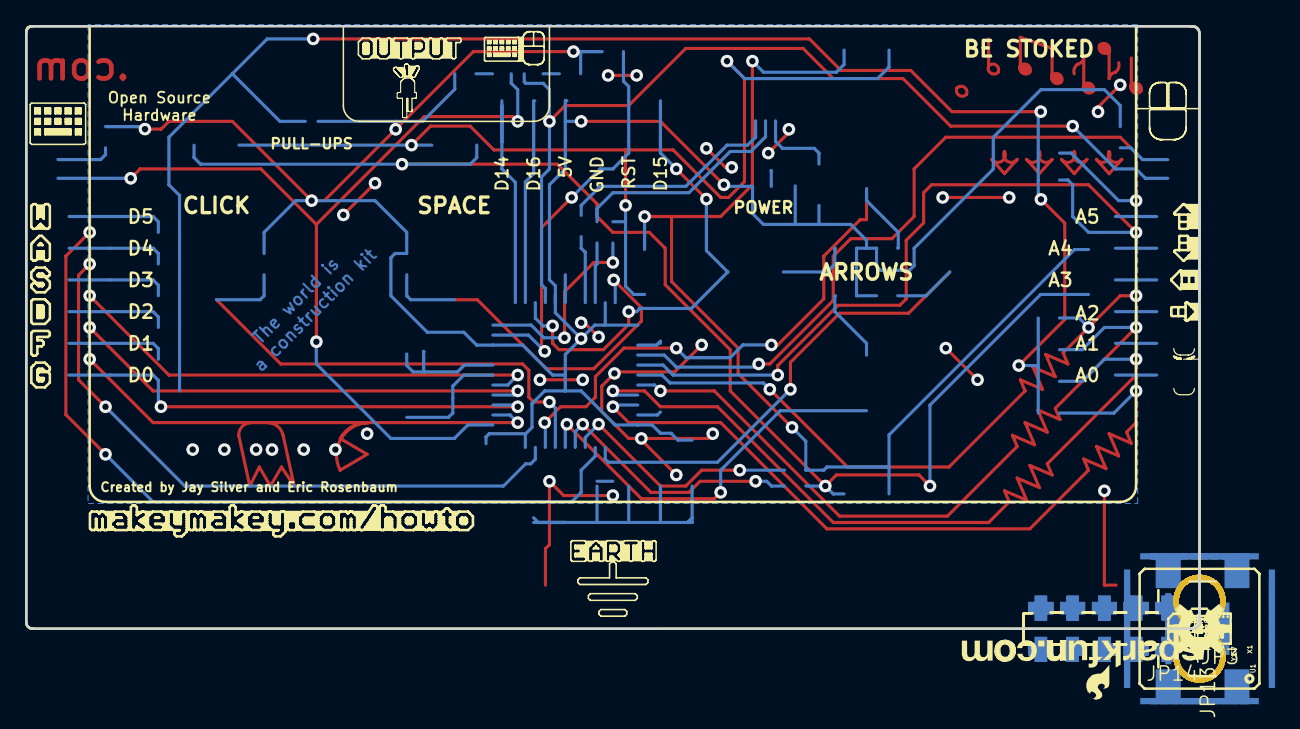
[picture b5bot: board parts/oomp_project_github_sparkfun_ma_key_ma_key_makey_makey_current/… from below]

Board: 2 copper layers, 94.0 x 48.3 mm, 73 parts (63 on the bottom side), 46 nets.
